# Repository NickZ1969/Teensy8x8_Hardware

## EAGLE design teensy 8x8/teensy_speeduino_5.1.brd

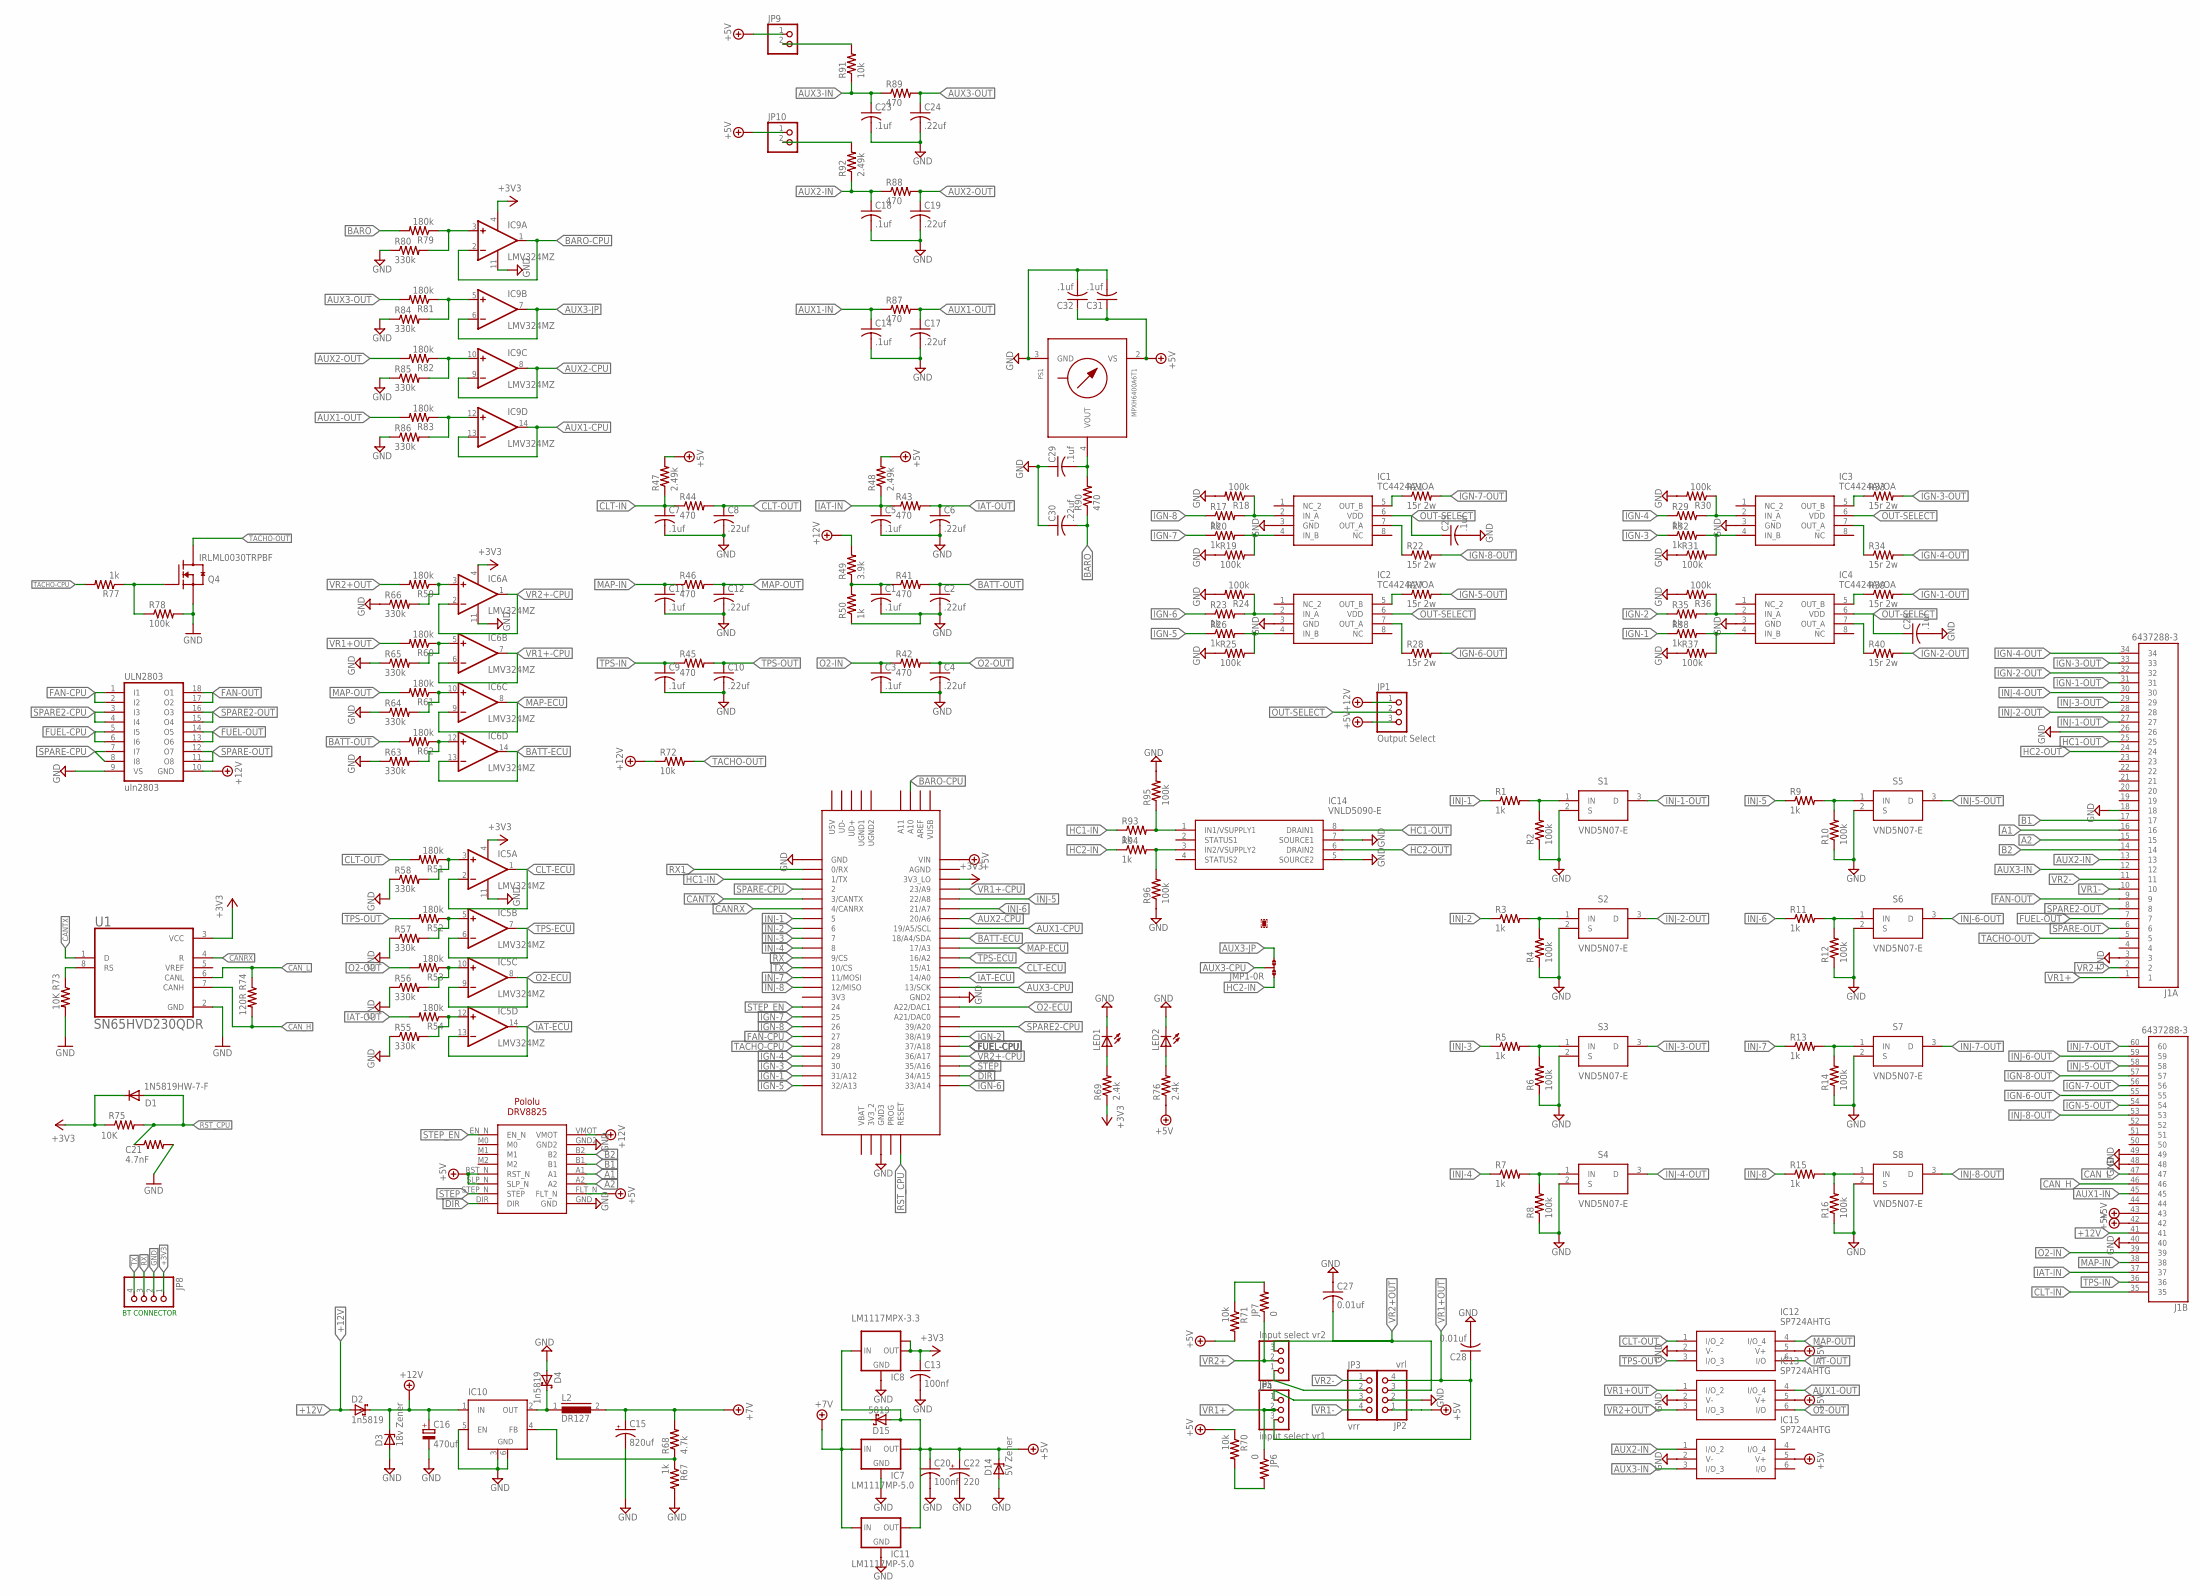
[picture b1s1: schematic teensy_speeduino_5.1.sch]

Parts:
C1, C3, C5, C7, C9, C11, C29, C31, C32: .1uf; C1206
C2, C4, C6, C8, C10, C12, C30: .22uf; C1206
C13, C20: 100nf; C1206
C14, C18, C23, C25, C26: .1uf; C0805
C15: 820uf; 153CLV-0810
C16: 470uf; 153CLV-0810
C17, C19, C24: .22uf; C0805
C21: 4.7nF; R1206
C22: 220; 153CLV-0605
C27, C28: 0.01uf; C1206
D1: 1N5819HW-7-F; SOD123
D2, D4: 1n5819; SMB
D3: 18v Zener; SMB
D14: 5V Zener; SMB
D15: 5819; SMB
IC1, IC2, IC3, IC4: TC4424AVOA; SOIC127P600X175-8N
IC5, IC6, IC9: LMV324MZ; TSSOP14
IC7, IC11: LM1117MP-5.0; SOT223
IC8: LM1117MPX-3.3; SOT223
IC10: LM2596S; TO263-5
IC12, IC13, IC15: SP724AHTG; SOT95P280X145-6N
IC14: VNLD5090-E; SOIC127P600X175-8N
J1: 6437288-3; TE_6437288-3
JMP1: 0R-JUMPA; A0R-JMP
JP1: Output Select; 1X03
JP2: vrl; 1X04
JP3: vrr; 1X04
JP4: Input select vr2; 1X03
JP5: input select vr1; 1X03
JP6, JP7: 0; R0805
JP8: PINHD-1X4; 1X04
JP9, JP10: PINHD-1X2; 1X02
L2: DR127
LED1, LED2: LEDSML1206; SML1206
PS1: MPXH6400A6T1; 1317
Q4: IRLML0030TRPBF; SOT95P280X135-3N
R1, R3, R5, R7, R9, R11, R13, R15, R17, R20, R23, R26, R29, R32, R35, R38, R50, R67, R77, R93, R94: 1k; R1206
R2, R4, R6, R8, R10, R12, R14, R16, R18, R19, R24, R25, R30, R31, R36, R37, R78, R95, R96: 100k; R1206
R21, R22, R27, R28, R33, R34, R39, R40: 15r 2w; R2512
R41, R42, R43, R44, R45, R46, R90: 470; R1206
R47, R48, R92: 2.49k; R1206
R49: 3.9k; R1206
R51, R52, R53, R54, R59, R60, R61, R62: 180k; R1206
R55, R56, R57, R58, R63, R64, R65, R66: 330k; R1206
R68: 4.7k; R1206
R69, R76: 2.4k; R1206
R70, R71, R72, R91: 10k; R1206
R73, R75: 10K; R1206
R74: 120R; R1206
R79, R81, R82, R83: 180k; R0805
R80, R84, R85, R86: 330k; R0805
R87, R88, R89: 470; R0805
S1, S2, S3, S4, S5, S6, S7, S8: VND5N07-E; TO-252-(DPAK)_1
U1: SN65HVD230QDR; SOIC127P600X175-8N
U$1: TEENSY_3.5/3.6
U$3: POLOLU-DRV8825
ULN2803: uln2803; SO18W

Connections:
+3V3: C13.1, D1.C, IC5.4 (V+), IC6.4 (V+), IC8.2 (OUT), IC8.TAB (OUT1), IC9.4 (V+), JP8.1, R69.1, R75.1, U1.3 (VCC), U$1.3V3_LO
+5V: C20.1, C22.+, C31.1, C32.1, D14.C, D15.A, IC7.2 (OUT), IC7.4 (OUT), IC8.3 (IN), IC11.2 (OUT), IC11.4 (OUT), IC12.5 (V+), IC13.5 (V+), IC15.5 (V+), J1.42, J1.43, JP1.3, JP2.1, JP9.1, JP10.1, PS1.2 (VS), R47.2, R48.2, R70.1, R71.2, R76.1, U$1.VIN, U$3.FLT_N, U$3.RST_N, U$3.SLP_N
+7V: C15.+, D15.C, IC7.3 (IN), IC11.3 (IN), L2.2, R68.2
+12V: C16.+, D2.A, D2.C, D3.C, IC10.1 (IN), J1.41, JP1.1, R49.2, R72.1, U$3.VMOT, ULN2803.10 (GND)
A1: J1.16, U$3.A1
A2: J1.15, U$3.A2
AUX1-CPU: IC9.13 (-IN), IC9.14 (OUT), U$1.19/A5/SCL
AUX1-IN: C14.1, J1.45, R87.1
AUX1-OUT: C17.1, IC13.4 (I/O_4), R83.2, R87.2
AUX2-CPU: IC9.8 (OUT), IC9.9 (-IN), U$1.20/A6
AUX2-IN: C18.1, IC15.1 (I/O_2), J1.13, R88.1, R92.1
AUX2-OUT: C19.1, R82.2, R88.2
AUX3-CPU: JMP1.2, U$1.13/SCK
AUX3-IN: C23.1, IC15.3 (I/O_3), J1.12, R89.1, R91.1
AUX3-JP: IC9.6 (-IN), IC9.7 (OUT), JMP1.3
AUX3-OUT: C24.1, R81.2, R89.2
B1: J1.17, U$3.B1
B2: J1.14, U$3.B2
BARO: C30.2, R79.2, R90.1
BARO-CPU: IC9.1 (OUT), IC9.2 (-IN), U$1.A10
BATT-ECU: IC6.13 (-IN), IC6.14 (OUT), U$1.18/A4/SDA
BATT-OUT: C2.1, R41.2, R62.2
CANRX: U1.4 (R), U$1.4/CANRX
CANTX: U1.1 (D), U$1.3/CANTX
CAN_H: J1.46, R74.2, U1.7 (CANH)
CAN_L: J1.47, R74.1, U1.6 (CANL)
CLT-ECU: IC5.1 (OUT), IC5.2 (-IN), U$1.15/A1
CLT-IN: C7.1, J1.35, R44.1, R47.1
CLT-OUT: C8.1, IC12.1 (I/O_2), R44.2, R51.2
DIR: U$1.34/A15, U$3.DIR
FAN-CPU: U$1.27, ULN2803.1 (I1), ULN2803.2 (I2)
FAN-OUT: J1.9, ULN2803.17 (O2), ULN2803.18 (O1)
FUEL-CPU: U$1.37/A18, ULN2803.5 (I5), ULN2803.6 (I6)
FUEL-OUT: J1.7, ULN2803.13 (O6), ULN2803.14 (O5)
GND: C1.2, C2.2, C3.2, C4.2, C5.2, C6.2, C7.2, C8.2, C9.2, C10.2, C11.2, C12.2, C13.2, C14.2, C15.-, C16.-, C17.2, C18.2, C19.2, C20.2, C21.2, C22.-, C23.2, C24.2, C25.2, C26.2, C27.1, C28.2, C29.1, C30.1, C31.2, C32.2, D3.A, D4.A, D14.A, IC1.3 (GND), IC2.3 (GND), IC3.3 (GND), IC4.3 (GND), IC5.11 (V-), IC6.11 (V-), IC7.1 (GND), IC8.1 (GND), IC9.11 (V-), IC10.3 (GND), IC10.5 (EN), IC10.6 (GND), IC11.1 (GND), IC12.2 (V-), IC13.2 (V-), IC14.5 (SOURCE2), IC14.7 (SOURCE1), IC15.2 (V-), J1.3, J1.18, J1.26, J1.40, J1.48, J1.49, JP2.2, JP8.2, LED1.C, LED2.C, PS1.3 (GND), Q4.2 (S), R2.1, R4.1, R6.1, R8.1, R10.1, R12.1, R14.1, R16.1, R18.2, R19.1, R24.2, R25.1, R30.2, R31.1, R36.2, R37.1, R50.1, R55.1, R56.1, R57.1, R58.1, R63.1, R64.1, R65.1, R66.1, R67.2, R73.2, R78.2, R80.1, R84.1, R85.1, R86.1, R95.2, R96.1, S1.2 (S), S2.2 (S), S3.2 (S), S4.2 (S), S5.2 (S), S6.2 (S), S7.2 (S), S8.2 (S), U1.2 (GND), U$1.GND, U$1.GND2, U$1.GND3, U$3.GND, U$3.GND2, ULN2803.9 (VS)
HC1-IN: R93.1, U$1.1/TX
HC1-OUT: IC14.8 (DRAIN1), J1.25
HC2-IN: JMP1.1, R94.1
HC2-OUT: IC14.6 (DRAIN2), J1.24
IAT-ECU: IC5.13 (-IN), IC5.14 (OUT), U$1.14/A0
IAT-IN: C5.1, J1.37, R43.1, R48.1
IAT-OUT: C6.1, IC12.6 (I/O), R43.2, R54.2
IGN-1: R38.1, U$1.31/A12
IGN-1-OUT: J1.31, R39.2
IGN-2: R35.1, U$1.38/A19
IGN-2-OUT: J1.32, R40.2
IGN-3: R32.1, U$1.30
IGN-3-OUT: J1.33, R33.2
IGN-4: R29.1, U$1.29
IGN-4-OUT: J1.34, R34.2
IGN-5: R26.1, U$1.32/A13
IGN-5-OUT: J1.54, R27.2
IGN-6: R23.1, U$1.33/A14
IGN-6-OUT: J1.55, R28.2
IGN-7: R20.1, U$1.25
IGN-7-OUT: J1.56, R21.2
IGN-8: R17.1, U$1.26
IGN-8-OUT: J1.57, R22.2
INJ-1: R1.1, U$1.5
INJ-1-OUT: J1.27, S1.3 (D)
INJ-2: R3.1, U$1.6
INJ-2-OUT: J1.28, S2.3 (D)
INJ-3: R5.1, U$1.7
INJ-3-OUT: J1.29, S3.3 (D)
INJ-4: R7.1, U$1.8
INJ-4-OUT: J1.30, S4.3 (D)
INJ-5: R9.1, U$1.22/A8
INJ-5-OUT: J1.58, S5.3 (D)
INJ-6: R11.1, U$1.21/A7
INJ-6-OUT: J1.59, S6.3 (D)
INJ-7: R13.1, U$1.11/MOSI
INJ-7-OUT: J1.60, S7.3 (D)
INJ-8: R15.1, U$1.12/MISO
INJ-8-OUT: J1.53, S8.3 (D)
MAP-ECU: IC6.8 (OUT), IC6.9 (-IN), U$1.17/A3
MAP-IN: C11.1, J1.38, R46.1
MAP-OUT: C12.1, IC12.4 (I/O_4), R46.2, R61.2
unnamed: R1.2, R2.2, S1.1 (IN)
unnamed: R3.2, R4.2, S2.1 (IN)
unnamed: JP3.3, JP5.1
unnamed: JP6.2, R70.2
unnamed: LED2.A, R76.2
unnamed: JP7.2, R71.1
unnamed: R5.2, R6.2, S3.1 (IN)
unnamed: IC1.7 (OUT_A), R22.1
unnamed: IC10.4 (FB), R67.1, R68.1
unnamed: R7.2, R8.2, S4.1 (IN)
unnamed: D4.C, IC10.2 (OUT), L2.1
unnamed: R73.1, U1.8 (RS)
unnamed: R9.2, R10.2, S5.1 (IN)
unnamed: LED1.A, R69.2
unnamed: Q4.1 (G), R77.1, R78.1
unnamed: R11.2, R12.2, S6.1 (IN)
unnamed: IC2.7 (OUT_A), R28.1
unnamed: IC9.3 (+IN), R79.1, R80.2
unnamed: R13.2, R14.2, S7.1 (IN)
unnamed: IC3.7 (OUT_A), R34.1
unnamed: JP10.2, R92.2
unnamed: R15.2, R16.2, S8.1 (IN)
unnamed: IC4.7 (OUT_A), R40.1
unnamed: C29.2, PS1.4 (VOUT), R90.2
unnamed: IC1.2 (IN_A), R17.2, R18.1
unnamed: IC1.4 (IN_B), R19.2, R20.2
unnamed: IC1.5 (OUT_B), R21.1
unnamed: IC14.1 (IN1/VSUPPLY1), R93.2, R95.1
unnamed: IC2.2 (IN_A), R23.2, R24.1
unnamed: IC2.4 (IN_B), R25.2, R26.2
unnamed: IC2.5 (OUT_B), R27.1
unnamed: JP3.2, JP4.1
unnamed: IC3.2 (IN_A), R29.2, R30.1
unnamed: IC3.4 (IN_B), R31.2, R32.2
unnamed: IC3.5 (OUT_B), R33.1
unnamed: IC14.3 (IN2/VSUPPLY2), R94.2, R96.2
unnamed: IC4.2 (IN_A), R35.2, R36.1
unnamed: IC4.4 (IN_B), R37.2, R38.2
unnamed: IC4.5 (OUT_B), R39.1
unnamed: JP9.2, R91.2
unnamed: IC6.3 (+IN), R59.1, R66.2
unnamed: C1.1, R41.1, R49.1, R50.2
unnamed: IC5.3 (+IN), R51.1, R58.2
unnamed: IC5.5 (+IN), R52.1, R57.2
unnamed: IC5.10 (+IN), R53.1, R56.2
unnamed: IC5.12 (+IN), R54.1, R55.2
unnamed: IC9.5 (+IN), R81.1, R84.2
unnamed: IC6.5 (+IN), R60.1, R65.2
unnamed: IC6.10 (+IN), R61.1, R64.2
unnamed: IC6.12 (+IN), R62.1, R63.2
unnamed: IC9.10 (+IN), R82.1, R85.2
unnamed: IC9.12 (+IN), R83.1, R86.2
O2-ECU: IC5.8 (OUT), IC5.9 (-IN), U$1.A22/DAC1
O2-IN: C3.1, J1.39, R42.1
O2-OUT: C4.1, IC13.6 (I/O), R42.2, R53.2
OUT-SELECT: C25.1, C26.1, IC1.6 (VDD), IC2.6 (VDD), IC3.6 (VDD), IC4.6 (VDD), JP1.2
RST_CPU: C21.1, D1.A, R75.2, U$1.RESET
RX: JP8.3, U$1.9/CS
RX1: U$1.0/RX
SPARE2-CPU: U$1.39/A20, ULN2803.3 (I3), ULN2803.4 (I4)
SPARE2-OUT: J1.8, ULN2803.15 (O4), ULN2803.16 (O3)
SPARE-CPU: U$1.2, ULN2803.7 (I7), ULN2803.8 (I8)
SPARE-OUT: J1.6, ULN2803.11 (O8), ULN2803.12 (O7)
STEP: U$1.35/A16, U$3.STEP_N (STEP)
STEP_EN: U$1.24, U$3.EN_N
TACHO-CPU: R77.2, U$1.28
TACHO-OUT: J1.5, Q4.3 (D), R72.2
TPS-ECU: IC5.6 (-IN), IC5.7 (OUT), U$1.16/A2
TPS-IN: C9.1, J1.36, R45.1
TPS-OUT: C10.1, IC12.3 (I/O_3), R45.2, R52.2
TX: JP8.4, U$1.10/CS
VR1+: J1.1, JP5.2, JP6.1
VR1+-CPU: IC6.6 (-IN), IC6.7 (OUT), U$1.23/A9
VR1+OUT: C28.1, IC13.1 (I/O_2), JP2.4, JP5.3, R60.2
VR1-: J1.10, JP3.4
VR2+: J1.2, JP4.2, JP7.1
VR2+-CPU: IC6.1 (OUT), IC6.2 (-IN), U$1.36/A17
VR2+OUT: C27.2, IC13.3 (I/O_3), JP2.3, JP4.3, R59.2
VR2-: J1.11, JP3.1

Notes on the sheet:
BT CONNECTOR

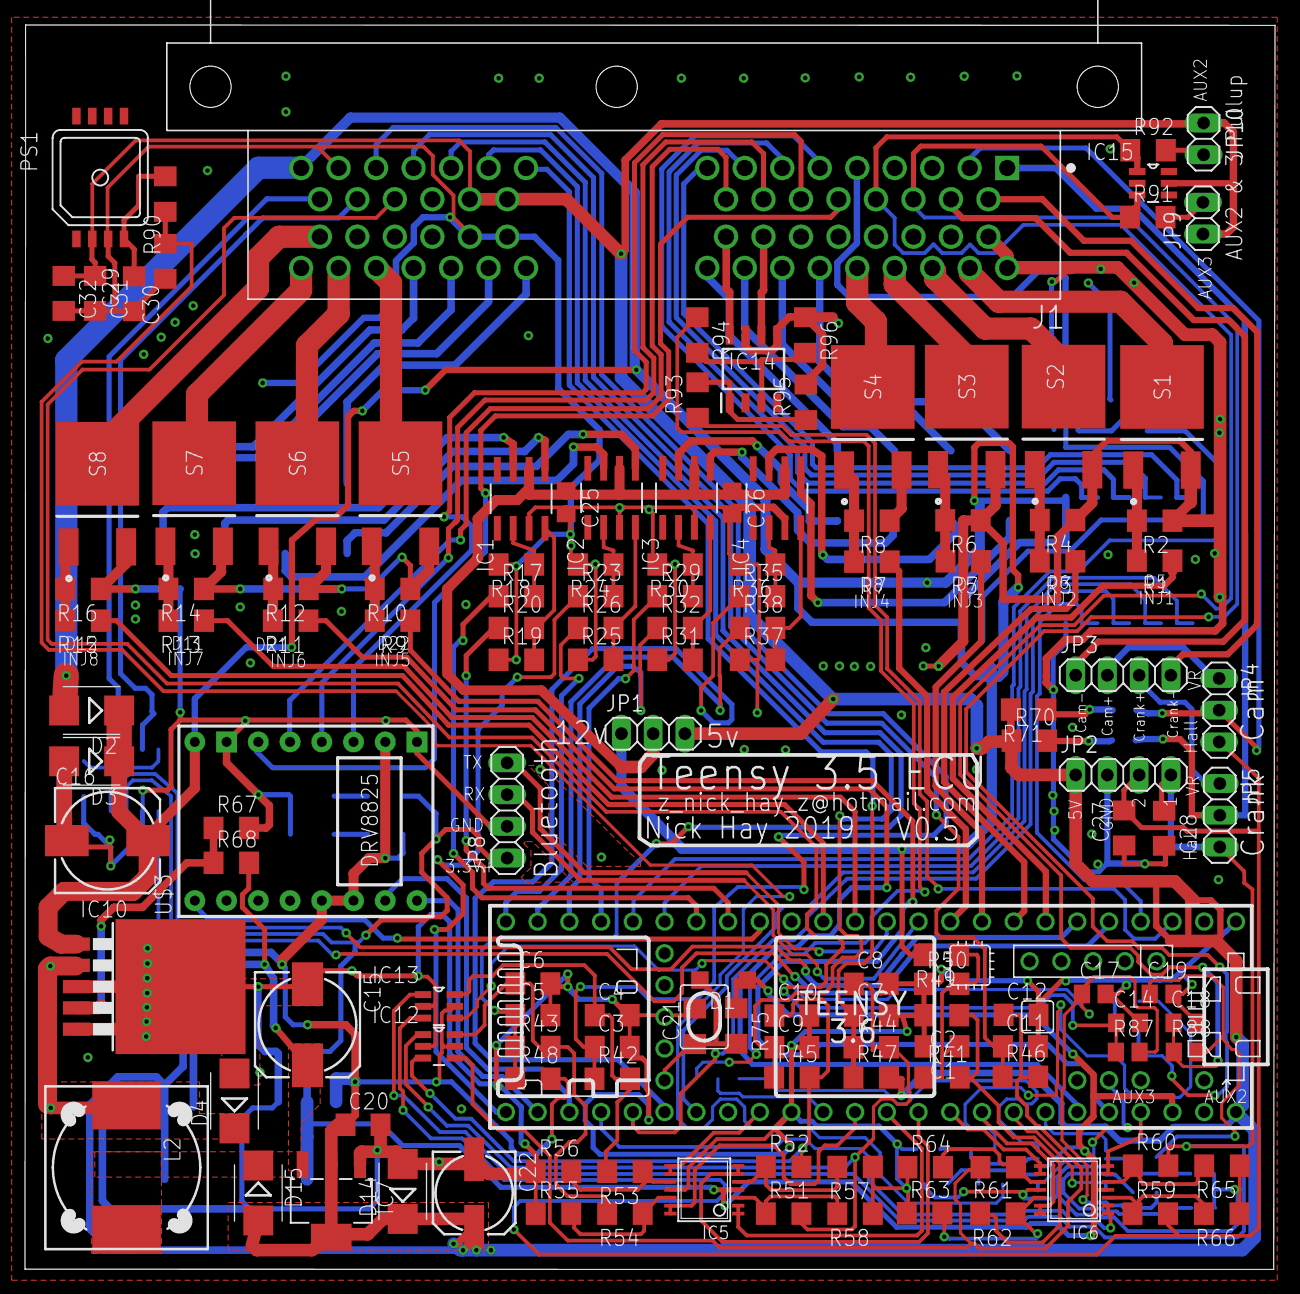
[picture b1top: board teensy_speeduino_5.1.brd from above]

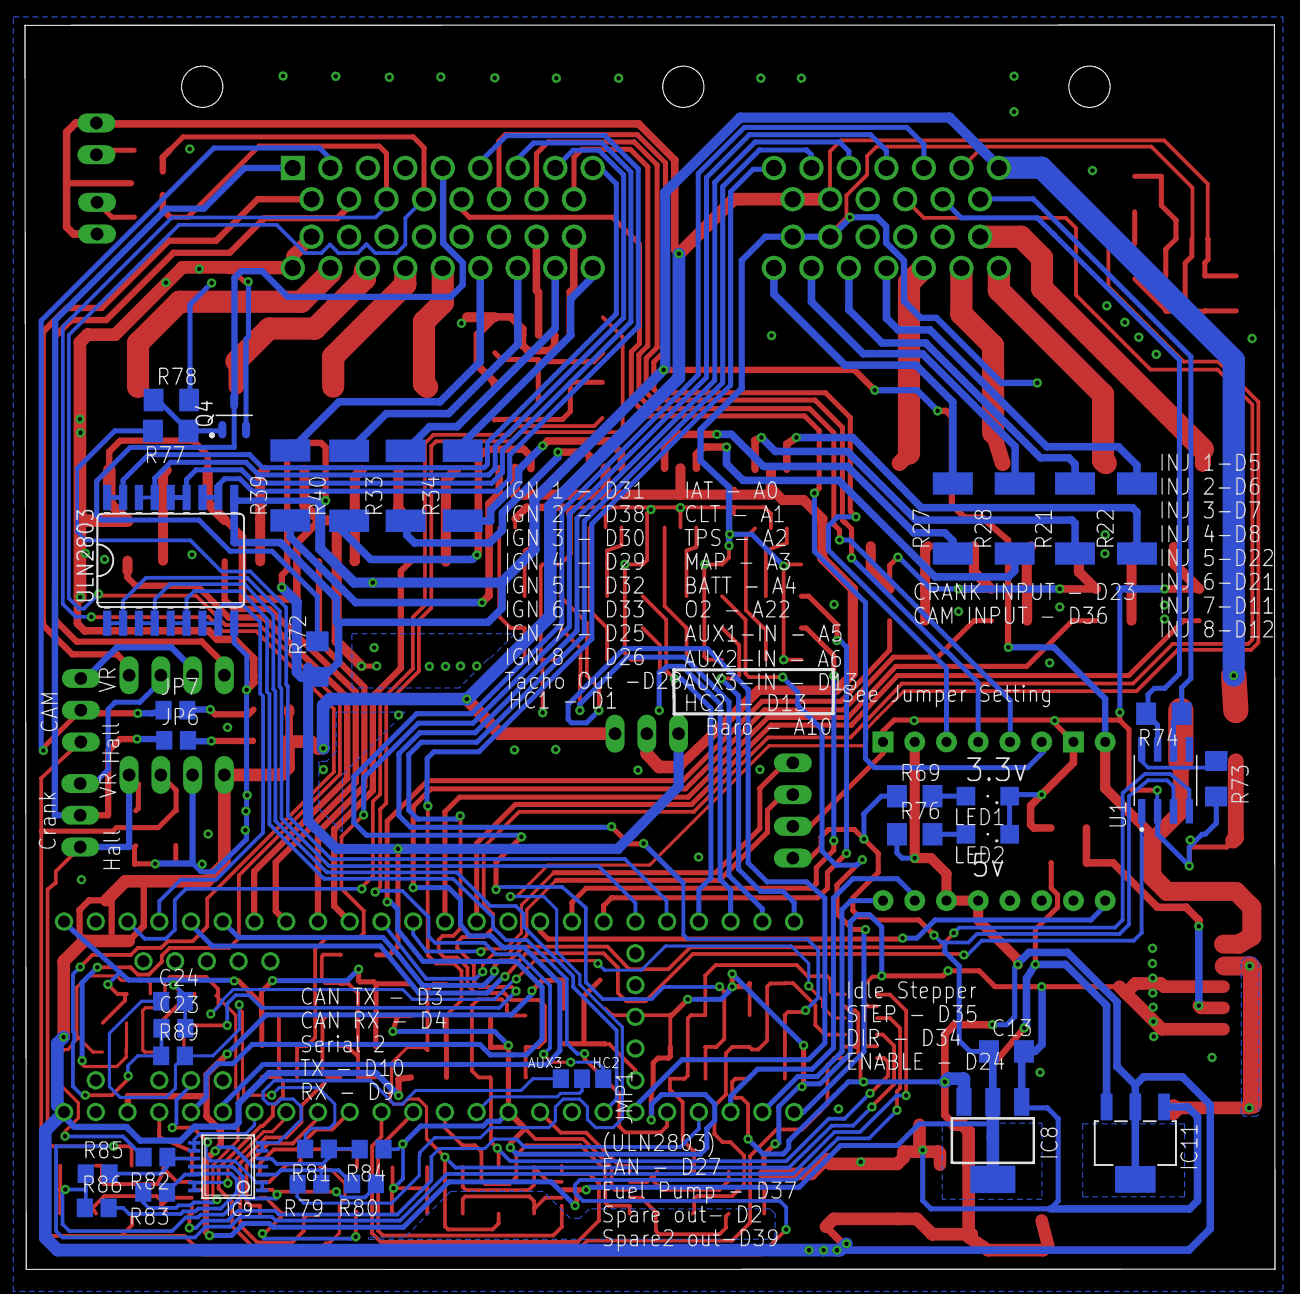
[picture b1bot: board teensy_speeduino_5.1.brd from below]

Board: 2 copper layers, 100.0 x 99.6 mm, 178 parts (38 on the bottom side), 155 nets.

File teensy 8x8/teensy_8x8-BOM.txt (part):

Partlist exported from /Users/hackintosh/Desktop/teensy_speeduino_1.1/teensy 8x8/teensy_speeduino_5.1.sch at 6/6/20 5:57 PM

Part    Value            Device             Package            Description                                                                                                                                                      
C1      .1uf             C-USC1206          C1206              CAPACITOR, American symbol                                                                                                                                       
C2      .22uf            C-USC1206          C1206              CAPACITOR, American symbol                                                                                                                                       
C3      .1uf             C-USC1206          C1206              CAPACITOR, American symbol                                                                                                                                       
C4      .22uf            C-USC1206          C1206              CAPACITOR, American symbol                                                                                                                                       
C5      .1uf             C-USC1206          C1206              CAPACITOR, American symbol                                                                                                                                       
C6      .22uf            C-USC1206          C1206              CAPACITOR, American symbol                                                                                                                                       
C7      .1uf             C-USC1206          C1206              CAPACITOR, American symbol                                                                                                                                       
C8      .22uf            C-USC1206          C1206              CAPACITOR, American symbol                                                                                                                                       
C9      .1uf             C-USC1206          C1206              CAPACITOR, American symbol                                                                                                                                       
C10     .22uf            C-USC1206          C1206              CAPACITOR, American symbol                                                                                                                                       
C11     .1uf             C-USC1206          C1206              CAPACITOR, American symbol                                                                                                                                       
C12     .22uf            C-USC1206          C1206              CAPACITOR, American symbol                                                                                                                                       
C13     100nf            C-USC1206          C1206              CAPACITOR, American symbol                                                                                                                                       
C14     .1uf             C-USC0805          C0805              CAPACITOR, American symbol                                                                                                                                       
C15     820uf            CPOL-US153CLV-0810 153CLV-0810        POLARIZED CAPACITOR, American symbol                                                                                                                             
C16     470uf            CPOL-EU153CLV-0810 153CLV-0810        POLARIZED CAPACITOR, European symbol                                                                                                                             
C17     .22uf            C-USC0805          C0805              CAPACITOR, American symbol                                                                                                                                       
C18     .1uf             C-USC0805          C0805              CAPACITOR, American symbol                                                                                                                                       
C19     .22uf            C-USC0805          C0805              CAPACITOR, American symbol                                                                                                                                       
C20     100nf            C-USC1206          C1206              CAPACITOR, American symbol                                                                                                                                       
C21     4.7nF            R-US_R1206         R1206              RESISTOR, American symbol                                                                                                                                        
C22     220              CPOL-US153CLV-0605 153CLV-0605        POLARIZED CAPACITOR, American symbol                                                                                                                             
C23     .1uf             C-USC0805          C0805              CAPACITOR, American symbol                                                                                                                                       
C24     .22uf            C-USC0805          C0805              CAPACITOR, American symbol                                                                                                                                       
C25     .1uf             C-USC0805          C0805              CAPACITOR, American symbol                                                                                                                                       
C26     .1uf             C-USC0805          C0805              CAPACITOR, American symbol                                                                                                                                       
C27     0.01uf           C-USC1206          C1206              CAPACITOR, American symbol                                                                                                                                       
C28     0.01uf           C-USC1206          C1206              CAPACITOR, American symbol                                                                                                                                       
C29     .1uf             C-USC1206          C1206              CAPACITOR, American symbol                                                                                                                                       
C30     .22uf            C-USC1206          C1206              CAPACITOR, American symbol                                                                                                                                       
C31     .1uf             C-USC1206          C1206              CAPACITOR, American symbol                                                                                                                                       
C32     .1uf             C-USC1206          C1206              CAPACITOR, American symbol                                                                                                                                       
D1      1N5819HW-7-F     DIODE-SOD123       SOD123             DIODE                                                                                                                                                            
D2      1n5819           SCHOTTKY-DIODESMD  SMB                Schottky Diode                                                                                                                                                   
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
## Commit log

2020-06-06 Teensy 8x8 Hardware
    Teensy 8x8 Hardware
    Made with Eaglecad
